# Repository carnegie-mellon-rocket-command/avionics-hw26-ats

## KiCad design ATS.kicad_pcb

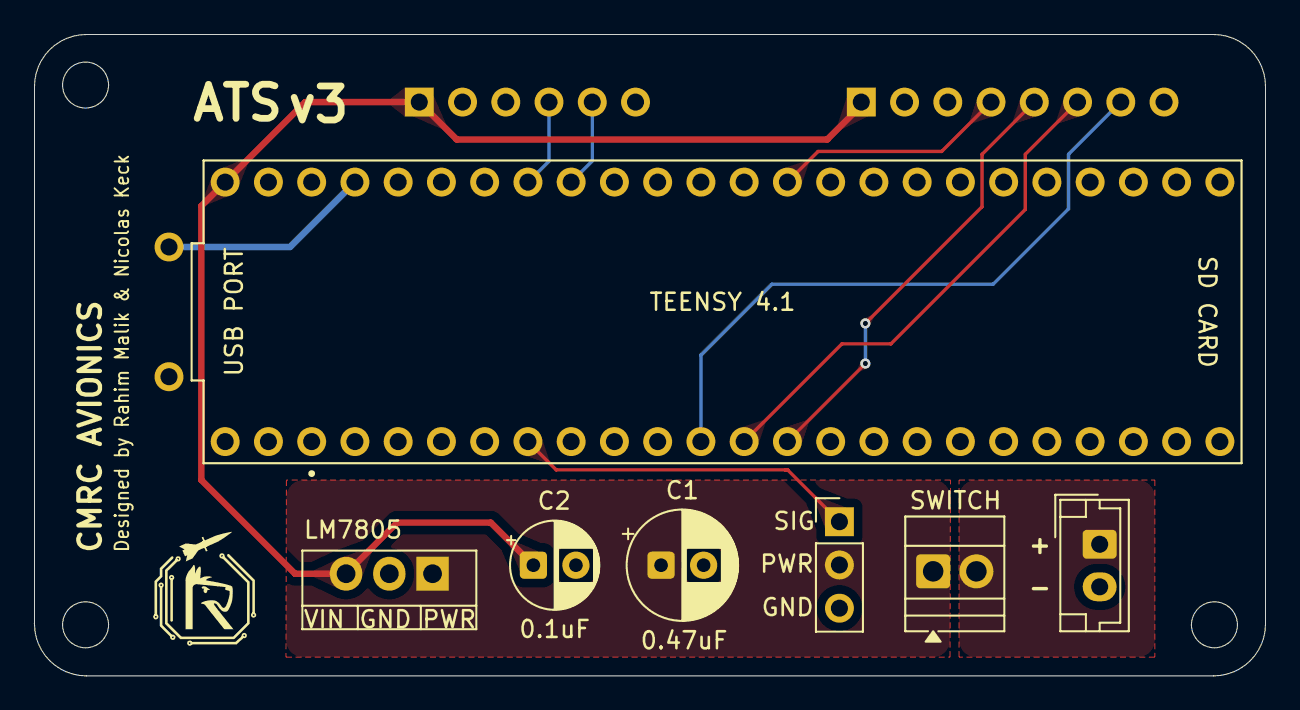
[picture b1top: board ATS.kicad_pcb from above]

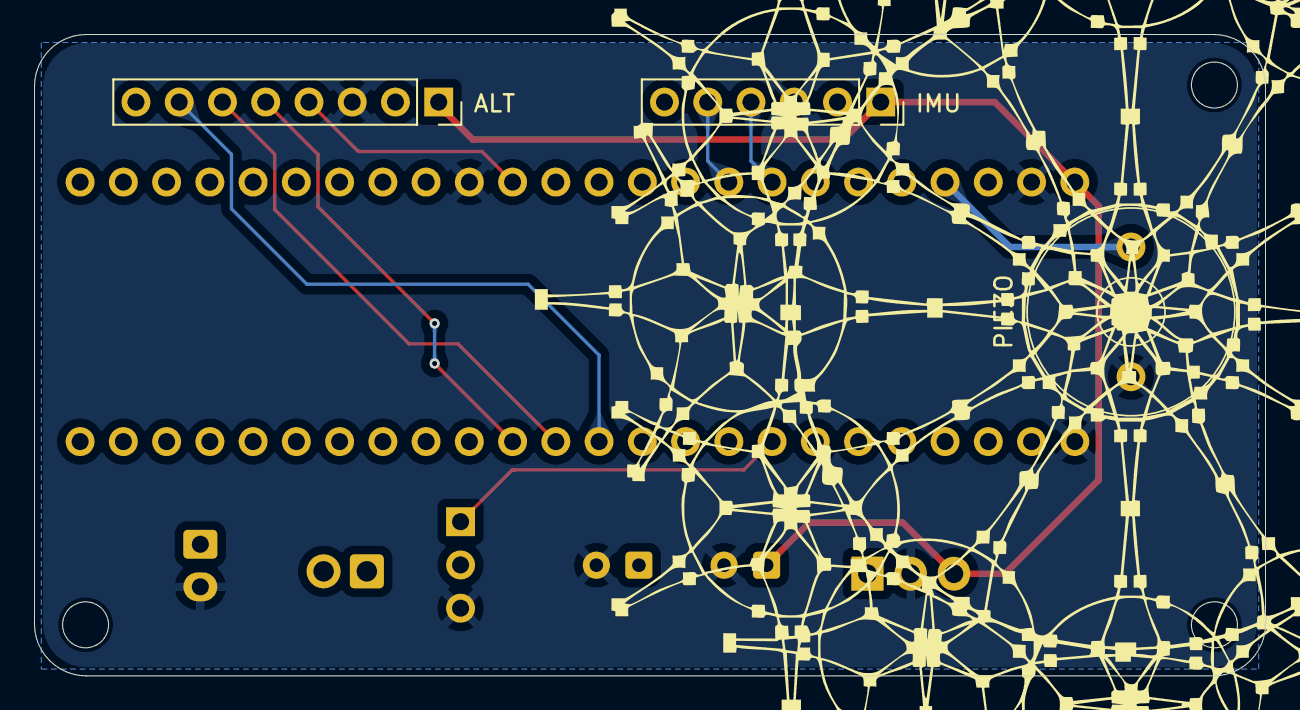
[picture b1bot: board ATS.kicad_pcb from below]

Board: 2 copper layers, 72.3 x 37.7 mm, 11 parts (3 on the bottom side), 12 nets.

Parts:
ADAFRUITBUZZER_1: AdafruitBuzzer
ALT_BMP_1: PinSocket_1x08_P2.54mm_Vertical
ATS_BUS_1: PinHeader_1x03_P2.54mm_Vertical
BAT_JST_1: JST_EH_B2B-EH-A_1x02_P2.50mm_Vertical
C1: 0.47uF; CP_Radial_D6.3mm_P2.50mm
C2: 0.1uF; CP_Radial_D5.0mm_P2.50mm
IMU_LSM6DSOX+LIS3MDL_1: PinSocket_1x06_P2.54mm_Vertical
LM7805_1: LM7805_TO220; TO-220-3_Vertical
SWITCH_SCREWTERM_1: TerminalBlock_Xinya_XY308-2.54-2P_1x02_P2.54mm_Horizontal
TEENSY4.1_1: Teensy4.1
svg2mod: G***; logo

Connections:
/ALT_CS: ALT_BMP_1.7, TEENSY4.1_1.10 (CS1)
/ALT_MISO: ALT_BMP_1.5, TEENSY4.1_1.12 (MISO)
/ALT_MOSI: ALT_BMP_1.6, TEENSY4.1_1.11 (MOSI)
/ALT_SCL: ALT_BMP_1.4, TEENSY4.1_1.13 (SCK)
/ATS_PWM: ATS_BUS_1.1, TEENSY4.1_1.6 (OUT1D)
/BAT: BAT_JST_1.1, SWITCH_SCREWTERM_1.2
/IMU_SCL: IMU_LSM6DSOX+LIS3MDL_1.4, TEENSY4.1_1.19 (A5)
/IMU_SDA: IMU_LSM6DSOX+LIS3MDL_1.5, TEENSY4.1_1.18 (A4)
/PIEZO: ADAFRUITBUZZER_1.P, TEENSY4.1_1.23 (A9)
/PWR: ATS_BUS_1.2, C1.1, LM7805_1.1 (VI), SWITCH_SCREWTERM_1.1
/VIN: ALT_BMP_1.1, C2.1, IMU_LSM6DSOX+LIS3MDL_1.1, LM7805_1.3 (VO), TEENSY4.1_1.VIN
GND: ADAFRUITBUZZER_1.N, ALT_BMP_1.3, ATS_BUS_1.3, BAT_JST_1.2, C1.2, C2.2, IMU_LSM6DSOX+LIS3MDL_1.3, LM7805_1.2 (GND), TEENSY4.1_1.GND1 (GND), TEENSY4.1_1.GND2 (GND), TEENSY4.1_1.GND3 (GND)

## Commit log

2025-12-25 init
2025-12-25 added gitignore
2025-12-26 updated libraries
2025-12-26 readded buzzer CAD
2025-12-27 incorporated libraries
2026-01-06 removed graphic
2026-01-20 finished review, sent to fab
